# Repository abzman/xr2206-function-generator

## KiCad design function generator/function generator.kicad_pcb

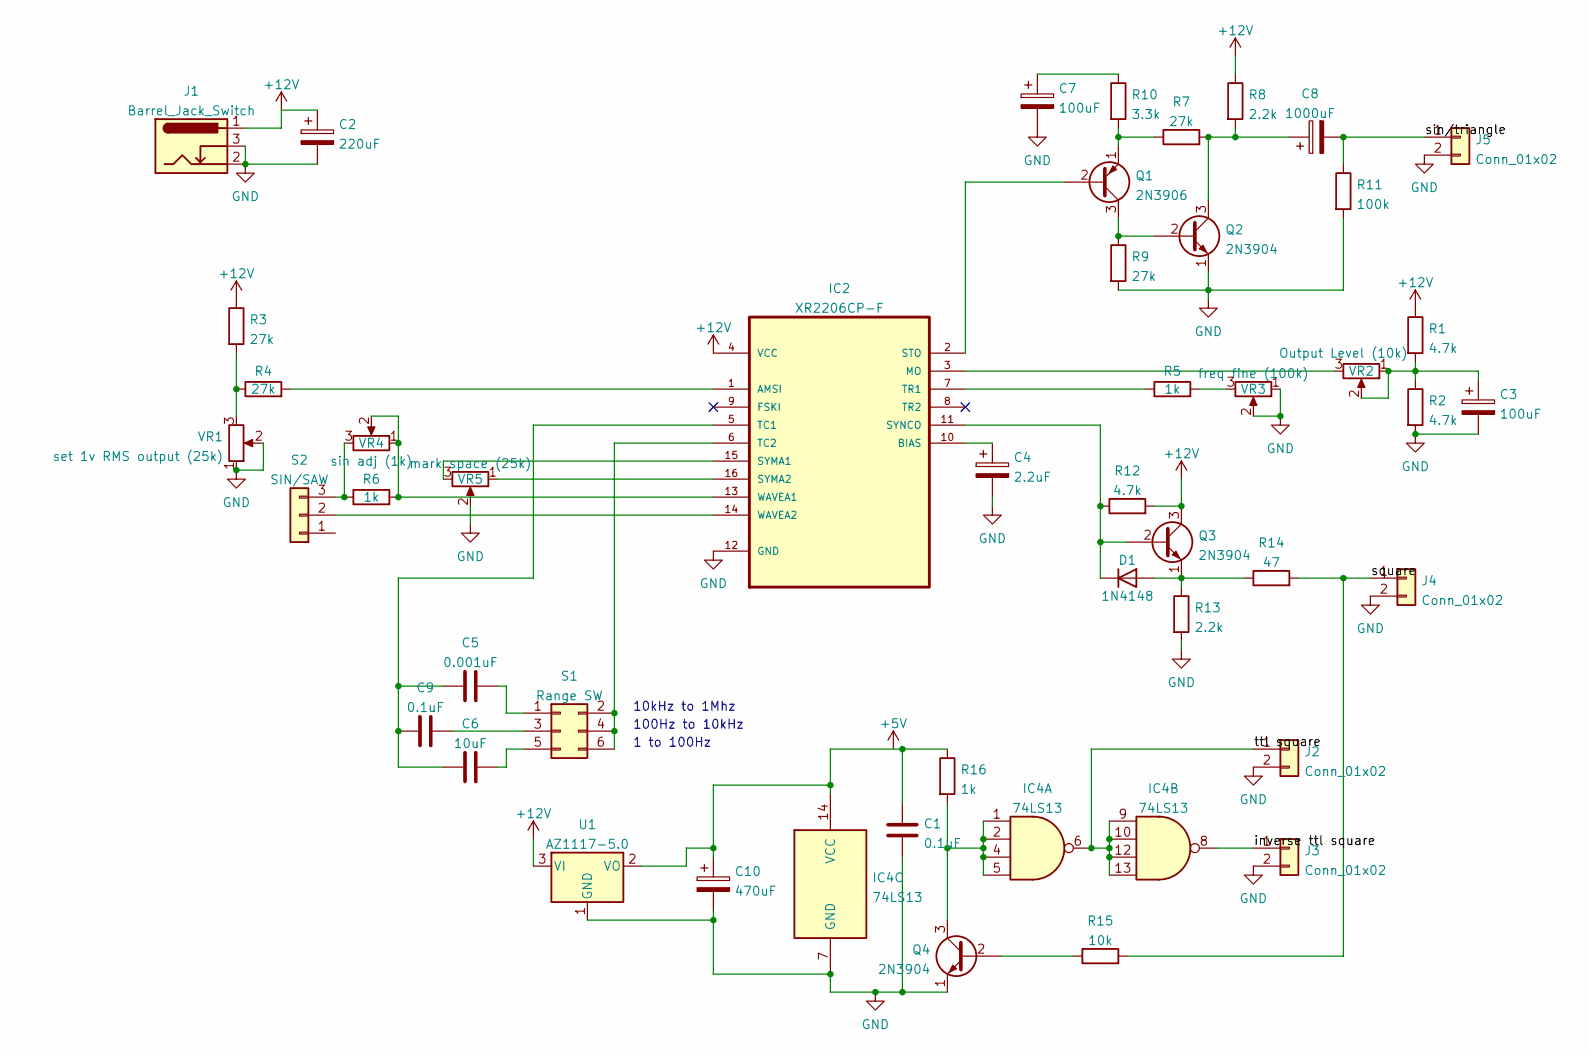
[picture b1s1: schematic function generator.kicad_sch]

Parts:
C1, C9: 0.1uF; C_0603_1608Metric
C2: 220uF; C_Disc_D3.8mm_W2.6mm_P2.50mm
C3, C7: 100uF; C_Disc_D3.8mm_W2.6mm_P2.50mm
C4: 2.2uF; C_Disc_D3.8mm_W2.6mm_P2.50mm
C5: 0.001uF; C_Disc_D3.8mm_W2.6mm_P2.50mm
C6: 10uF; C_Disc_D3.8mm_W2.6mm_P2.50mm
C8: 1000uF; C_Disc_D3.8mm_W2.6mm_P2.50mm
C10: 470uF; C_Disc_D3.8mm_W2.6mm_P2.50mm
D1: 1N4148; D_DO-35_SOD27_P7.62mm_Horizontal
IC2: XR2206CP-F; DIP-16_W7.62mm; MPN XR2206CP-F
IC4: 74LS13; DIP-14_W7.62mm
J1: Barrel_Jack_Switch; BarrelJack_Horizontal
J2, J3, J4, J5: Conn_01x02; PinHeader_1x02_P2.54mm_Vertical
Q1: 2N3906; TO-92_Inline
Q2, Q3, Q4: 2N3904; TO-92_Inline
R1, R2, R12: 4.7k; R_0603_1608Metric
R3, R4, R7, R9: 27k; R_0603_1608Metric
R5, R6, R16: 1k; R_0603_1608Metric
R8, R13: 2.2k; R_0603_1608Metric
R10: 3.3k; R_0603_1608Metric
R11: 100k; R_0603_1608Metric
R14: 47; R_0603_1608Metric
R15: 10k; R_0603_1608Metric
S1: Range SW; PinHeader_2x03_P2.54mm_Vertical
S2: SIN/SAW; PinHeader_1x03_P2.54mm_Vertical
U1: AZ1117-5.0; SOT-223-3_TabPin2
VR1: set 1v RMS output (25k); Potentiometer_Bourns_3386F_Vertical
VR2: Output Level (10k); Potentiometer_Bourns_3386F_Vertical
VR3: freq fine (100k); Potentiometer_Bourns_3386F_Vertical
VR4: sin adj (1k); Potentiometer_Bourns_3386F_Vertical
VR5: mark space (25k); Potentiometer_Bourns_3386F_Vertical

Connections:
+12V: C2.1, IC2.4 (VCC), J1.1, Q3.3 (C), R1.1, R3.1, R8.1, R12.2, U1.3 (VI)
/inverse ttl square: IC4.8, J3.1
/sin/triangle: C8.2, J5.1, R11.1
/square: J4.1, R14.2, R15.2
/ttl square: IC4.6, IC4.9, IC4.10, IC4.12, IC4.13, J2.1
GND: C1.2, C2.2, C3.2, C4.2, C7.2, C10.2, IC2.12 (GND), IC4.7 (GND), J1.2, J1.3, J2.2, J3.2, J4.2, J5.2, Q2.1 (E), Q4.1 (E), R2.2, R9.2, R11.2, R13.2, U1.1 (GND), VR1.1, VR1.2, VR3.1, VR3.2, VR5.2
unnamed: C4.1, IC2.10 (BIAS)
unnamed: C5.1, C6.1, C9.1, IC2.5 (TC1)
unnamed: C5.2, S1.1
unnamed: C6.2, S1.5
unnamed: C7.1, R10.1
unnamed: C9.2, S1.3
unnamed: IC2.6 (TC2), S1.2, S1.4, S1.6
unnamed: IC2.15 (SYMA1), VR5.3
unnamed: IC2.16 (SYMA2), VR5.1
unnamed: IC4.1, IC4.2, IC4.4, IC4.5, Q4.3 (C), R16.2
unnamed: C1.1, C10.1, IC4.14 (VCC), R16.1, U1.2 (VO)
unnamed: IC2.2 (STO), Q1.2 (B)
unnamed: Q1.3 (C), Q2.2 (B), R9.1
unnamed: C8.1, Q2.3 (C), R7.2, R8.2
unnamed: D1.2 (A), Q3.1 (E), R13.1, R14.1
unnamed: Q4.2 (B), R15.1
unnamed: R3.2, R4.1, VR1.3
unnamed: IC2.1 (AMSI), R4.2
unnamed: IC2.7 (TR1), R5.1
unnamed: R5.2, VR3.3
unnamed: R6.1, S2.3, VR4.3
unnamed: Q1.1 (E), R7.1, R10.2
unnamed: D1.1 (K), IC2.11 (SYNCO), Q3.2 (B), R12.1
unnamed: IC2.14 (WAVEA2), S2.2
unnamed: C3.1, R1.2, R2.1, VR2.1, VR2.2
unnamed: IC2.3 (MO), VR2.3
unnamed: IC2.13 (WAVEA1), R6.2, VR4.1, VR4.2

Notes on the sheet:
1 to 100Hz
100Hz to 10kHz
10kHz to 1Mhz

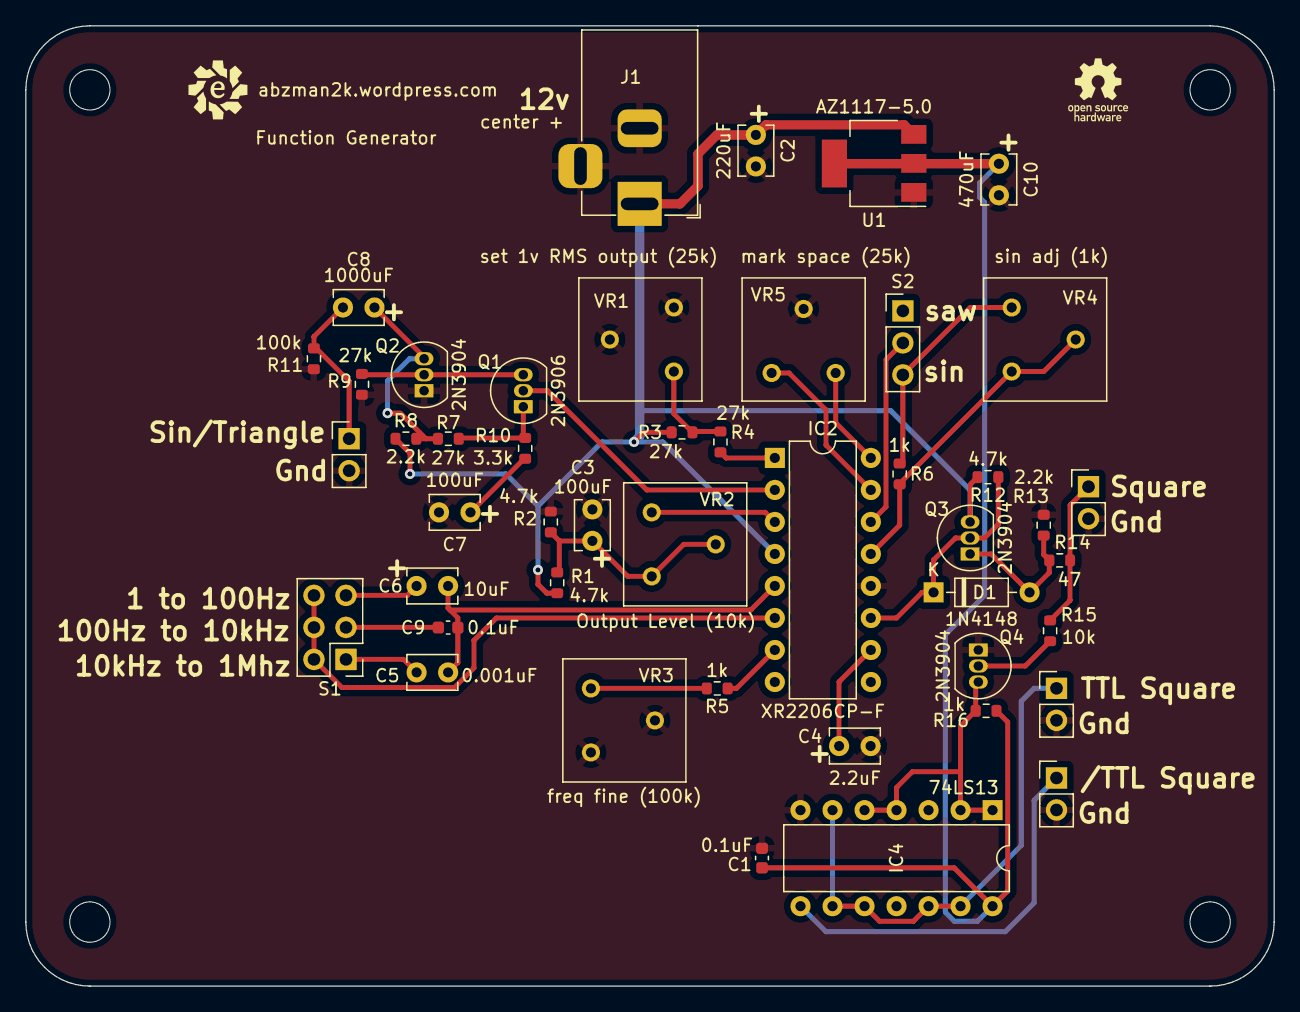
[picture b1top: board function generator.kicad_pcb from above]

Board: 2 copper layers, 99.1 x 76.2 mm, 46 parts (0 on the bottom side), 33 nets.

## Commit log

2022-01-25 first board rev
2022-11-25 added gitignore
